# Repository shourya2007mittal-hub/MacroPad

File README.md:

# MicroPad Air1

This is a Custom Xiao Rp2040  Based MicroPad , It has 8 Switches , a roter encode and an 0.91 inch  oled screen . 
We used matrix for switches so it uses less gpio pins and it has 3 layers the rotor key is used to change the layers
and the selected layer is  displaced on the screen.so in total we have  keys output 8x4=32 outputs.

## Features

- Based on Xiao Rp2040
- Has total 32 Outputs
-  Uses Keyboard Matrix

-  ## Firmware
- Firmware is based on QMK.

- # Bill of Materials (BOM)

| Item | Price (USD) | Source |
|------|------------:|--------|
| PCB + Shipping (after coupons) | 9.73 | JLCPCB |
| Xiao RP2040 + Shipping | 7.17 | https://robocraze.com/products/seeed-studio-xiao-rp2040-development-board |
| Keycaps (Pack of 5) ×2 | 2.15 | https://meckeys.com/shop/accessories/keyboard-accessories/keycaps/blank/blank-dsa-keycaps-1u/ |
| Switches (Pack of 10) | 2.15 | https://neomacro.in/products/hmx-snowfall-tactile-switch |
| Hot-Swap Sockets (Pack of 10) | 0.86 | https://meckeys.com/shop/accessories/keyboard-accessories/key-switches/kailh-hot-swap-socket/ |
| Meckeys Shipping | 1.10 | https://meckeys.com |
| Diodes (10 pcs) | Already have | — |
| Rotary Encoder | Already have | — |
| **Total** | **21.01** | |

### Schematic<br><br>

###  PCB Design<br><br>

### Case<br><br>

### 3D Render <br><br>

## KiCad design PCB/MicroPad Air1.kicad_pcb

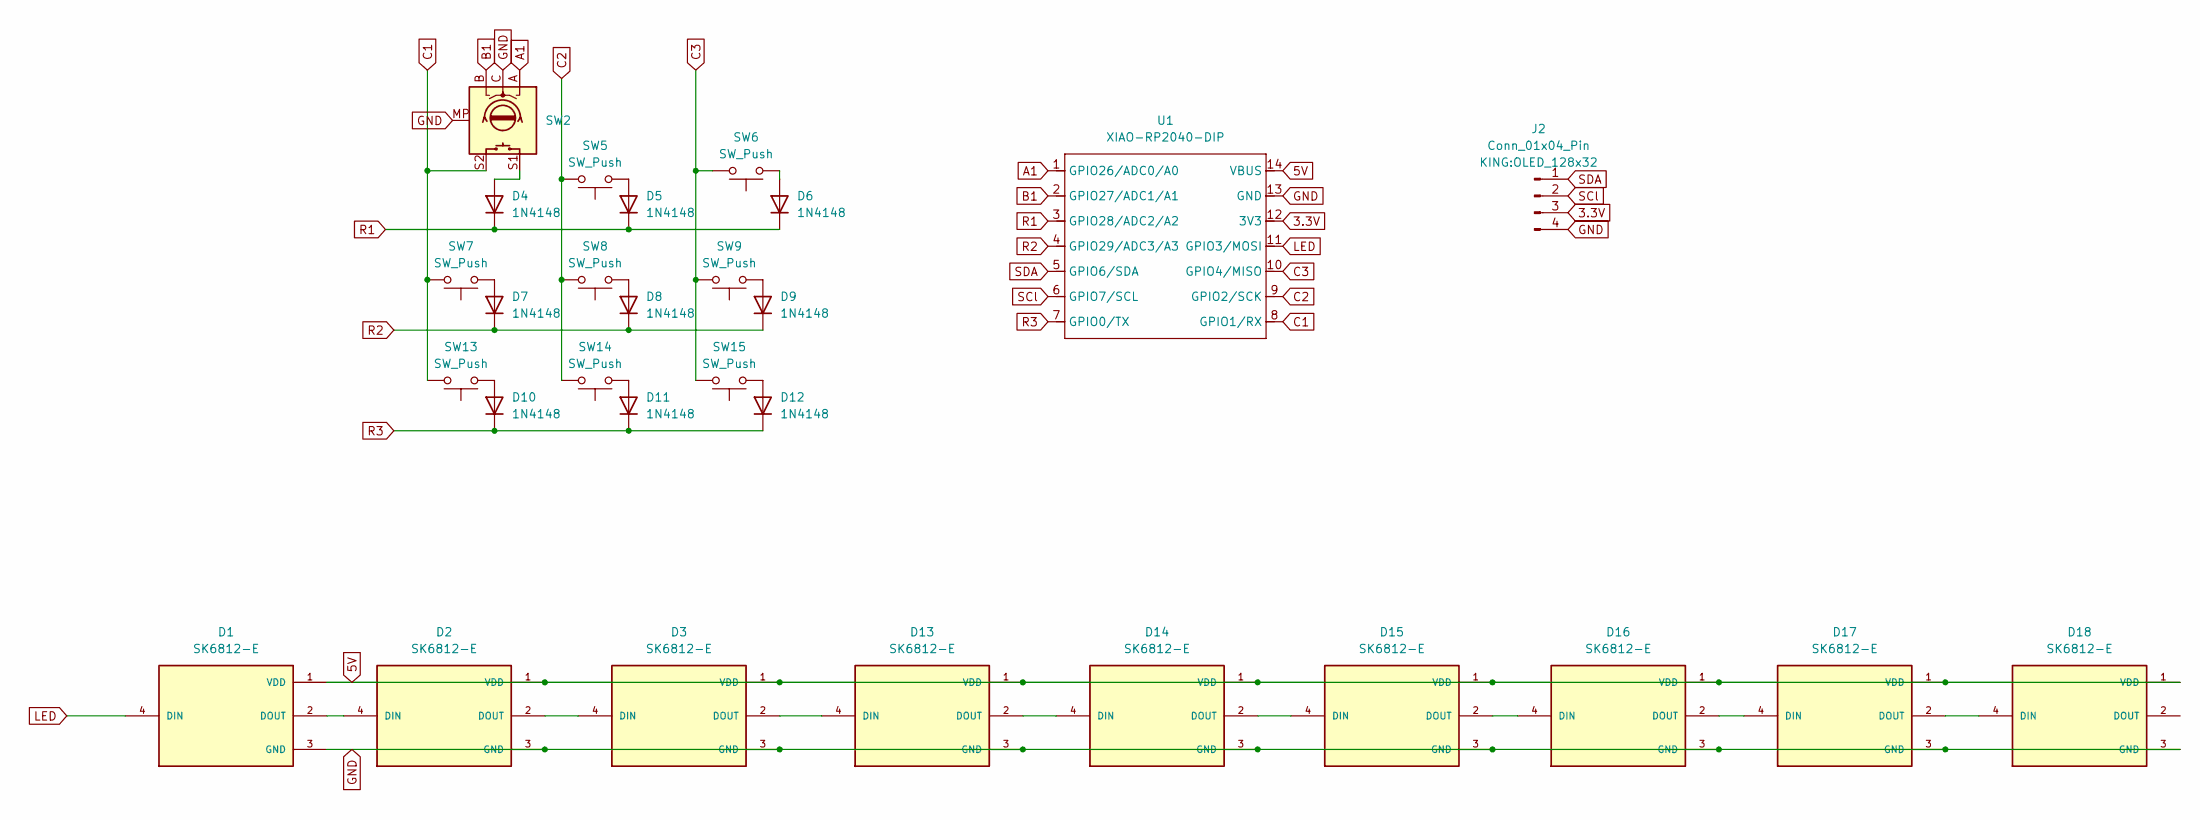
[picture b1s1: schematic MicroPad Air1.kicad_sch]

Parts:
D1, D2, D3, D13, D14, D15, D16, D17, D18: SK6812-E; LED_SK6812-E; PARTREV 2
D4, D5, D6, D7, D8, D9, D10, D11, D12: 1N4148; D_DO-35_SOD27_P7.62mm_Horizontal
J2: Conn_01x04_Pin; OLED_128x32
SW2: RotaryEncoder_Switch_MP; RotaryEncoder_Alps_EC11E-Switch_Vertical_H20mm
SW5, SW6, SW7, SW8, SW9, SW13, SW14, SW15: SW_Push; MX100H
U1: XIAO-RP2040-DIP

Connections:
3.3V: J2.3, U1.12 (3V3)
5V: D1.1 (VDD), D2.1 (VDD), D3.1 (VDD), D13.1 (VDD), D14.1 (VDD), D15.1 (VDD), D16.1 (VDD), D17.1 (VDD), D18.1 (VDD), U1.14 (VBUS)
A1: SW2.A, U1.1 (GPIO26/ADC0/A0)
B1: SW2.B, U1.2 (GPIO27/ADC1/A1)
C1: SW2.S2, SW7.2, SW13.2, U1.8 (GPIO1/RX)
C2: SW5.2, SW8.2, SW14.2, U1.9 (GPIO2/SCK)
C3: SW6.2, SW9.2, SW15.2, U1.10 (GPIO4/MISO)
GND: D1.3 (GND), D2.3 (GND), D3.3 (GND), D13.3 (GND), D14.3 (GND), D15.3 (GND), D16.3 (GND), D17.3 (GND), D18.3 (GND), J2.4, SW2.C, SW2.MP, U1.13 (GND)
LED: D1.4 (DIN), U1.11 (GPIO3/MOSI)
unnamed: D1.2 (DOUT), D2.4 (DIN)
unnamed: D2.2 (DOUT), D3.4 (DIN)
unnamed: D4.2 (A), SW2.S1
unnamed: D5.2 (A), SW5.1
unnamed: D6.2 (A), SW6.1
unnamed: D7.2 (A), SW7.1
unnamed: D8.2 (A), SW8.1
unnamed: D9.2 (A), SW9.1
unnamed: D10.2 (A), SW13.1
unnamed: D11.2 (A), SW14.1
unnamed: D12.2 (A), SW15.1
unnamed: D3.2 (DOUT), D13.4 (DIN)
unnamed: D13.2 (DOUT), D14.4 (DIN)
unnamed: D14.2 (DOUT), D15.4 (DIN)
unnamed: D15.2 (DOUT), D16.4 (DIN)
unnamed: D16.2 (DOUT), D17.4 (DIN)
unnamed: D17.2 (DOUT), D18.4 (DIN)
R1: D4.1 (K), D5.1 (K), D6.1 (K), U1.3 (GPIO28/ADC2/A2)
R2: D7.1 (K), D8.1 (K), D9.1 (K), U1.4 (GPIO29/ADC3/A3)
R3: D10.1 (K), D11.1 (K), D12.1 (K), U1.7 (GPIO0/TX)
SCl: J2.2, U1.6 (GPIO7/SCL)
SDA: J2.1, U1.5 (GPIO6/SDA)

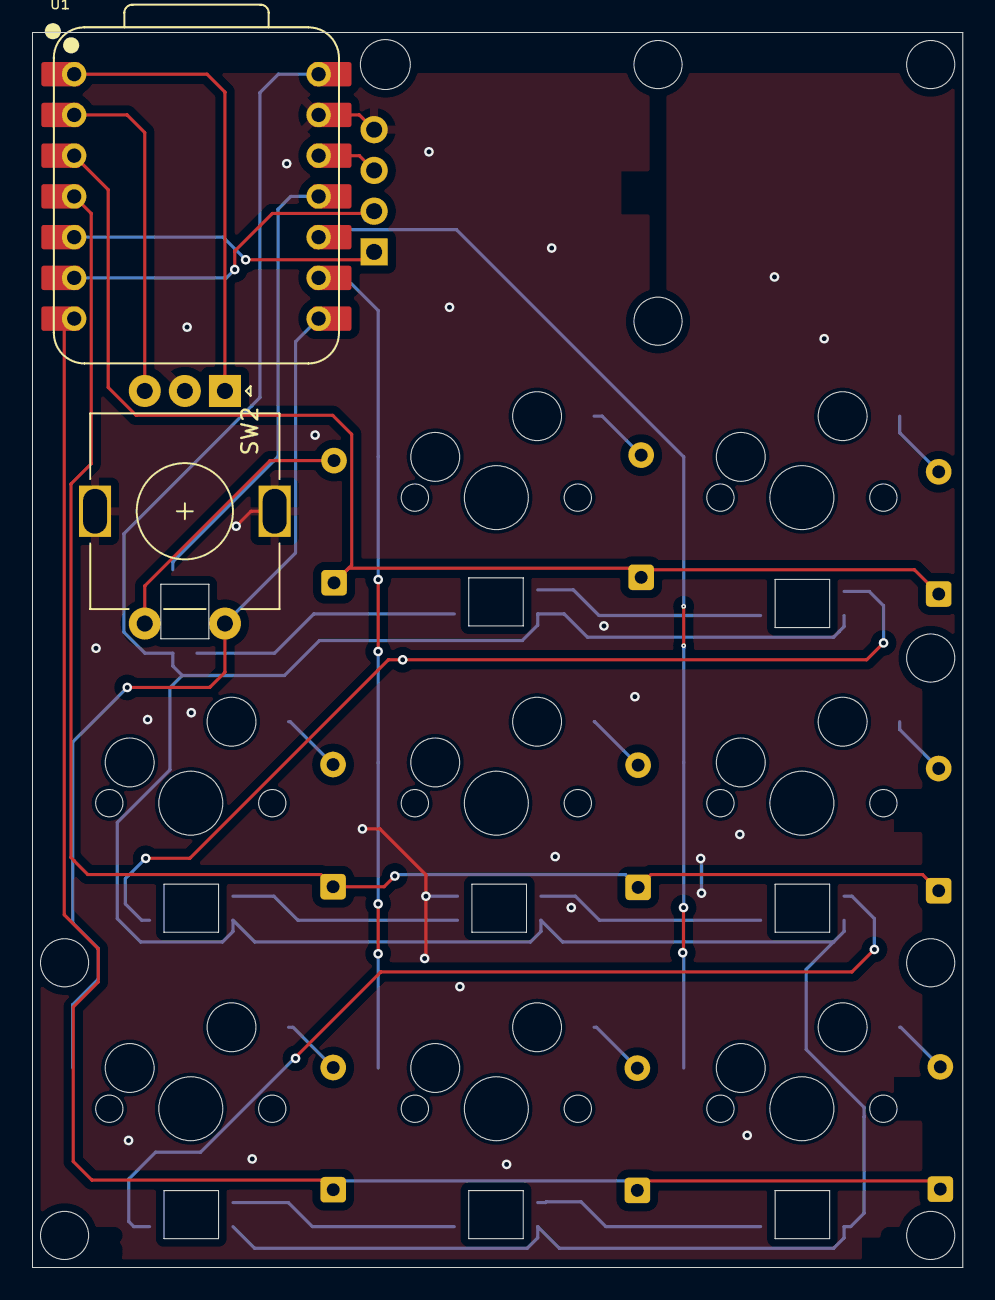
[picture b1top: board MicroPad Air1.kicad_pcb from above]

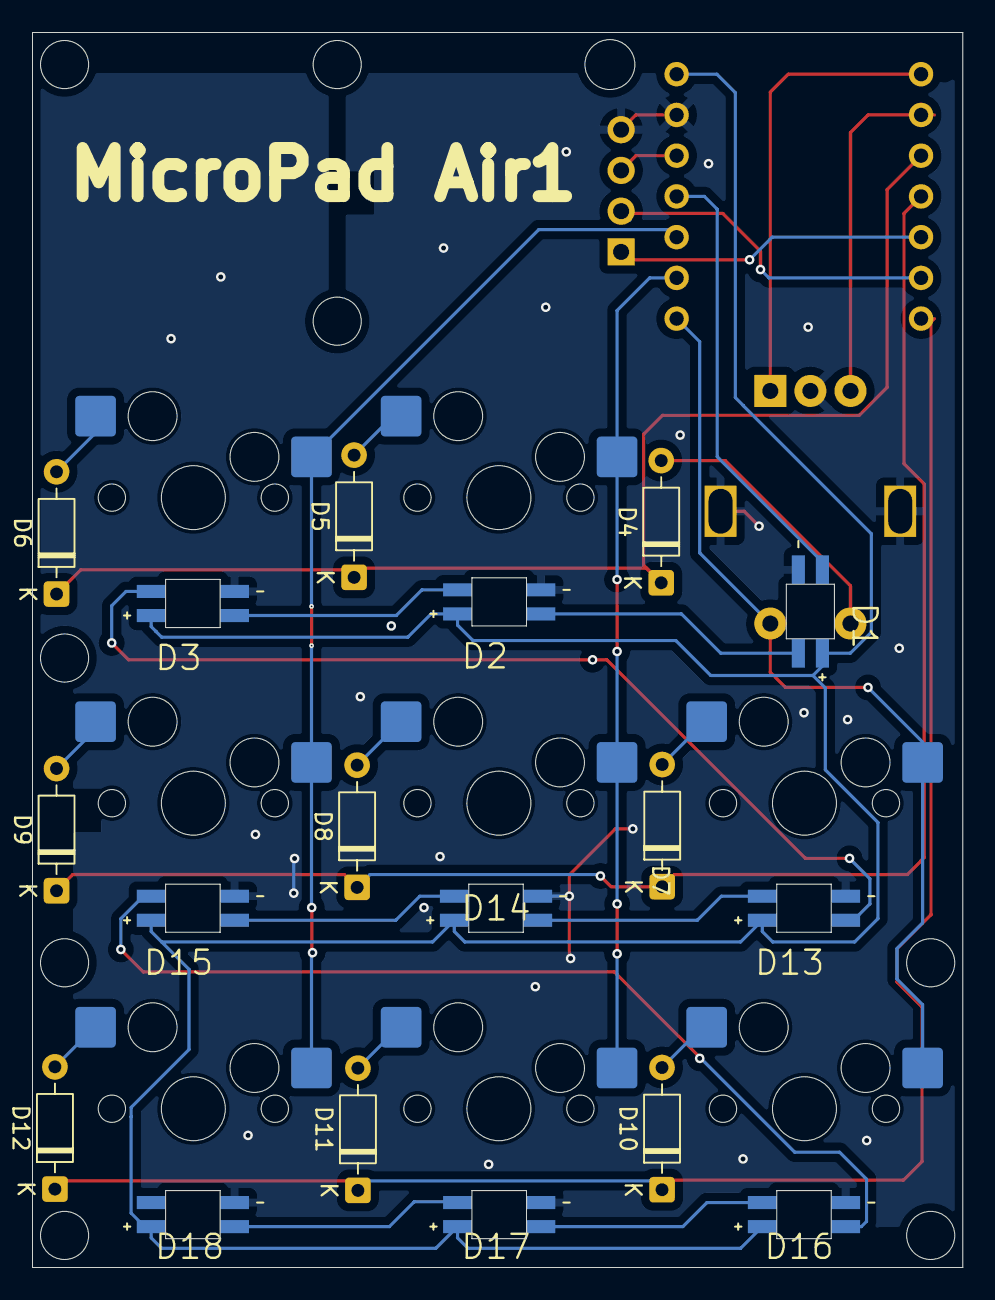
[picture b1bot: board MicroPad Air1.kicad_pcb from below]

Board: 2 copper layers, 58.0 x 77.0 mm, 29 parts (26 on the bottom side), 31 nets.
